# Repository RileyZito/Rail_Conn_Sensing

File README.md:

# Rail_Conn_Sensing
A circuit to sense which forks of a train track are connected for a minature train set

## Engineers
@RileyZito and @wwc559

## Subpages

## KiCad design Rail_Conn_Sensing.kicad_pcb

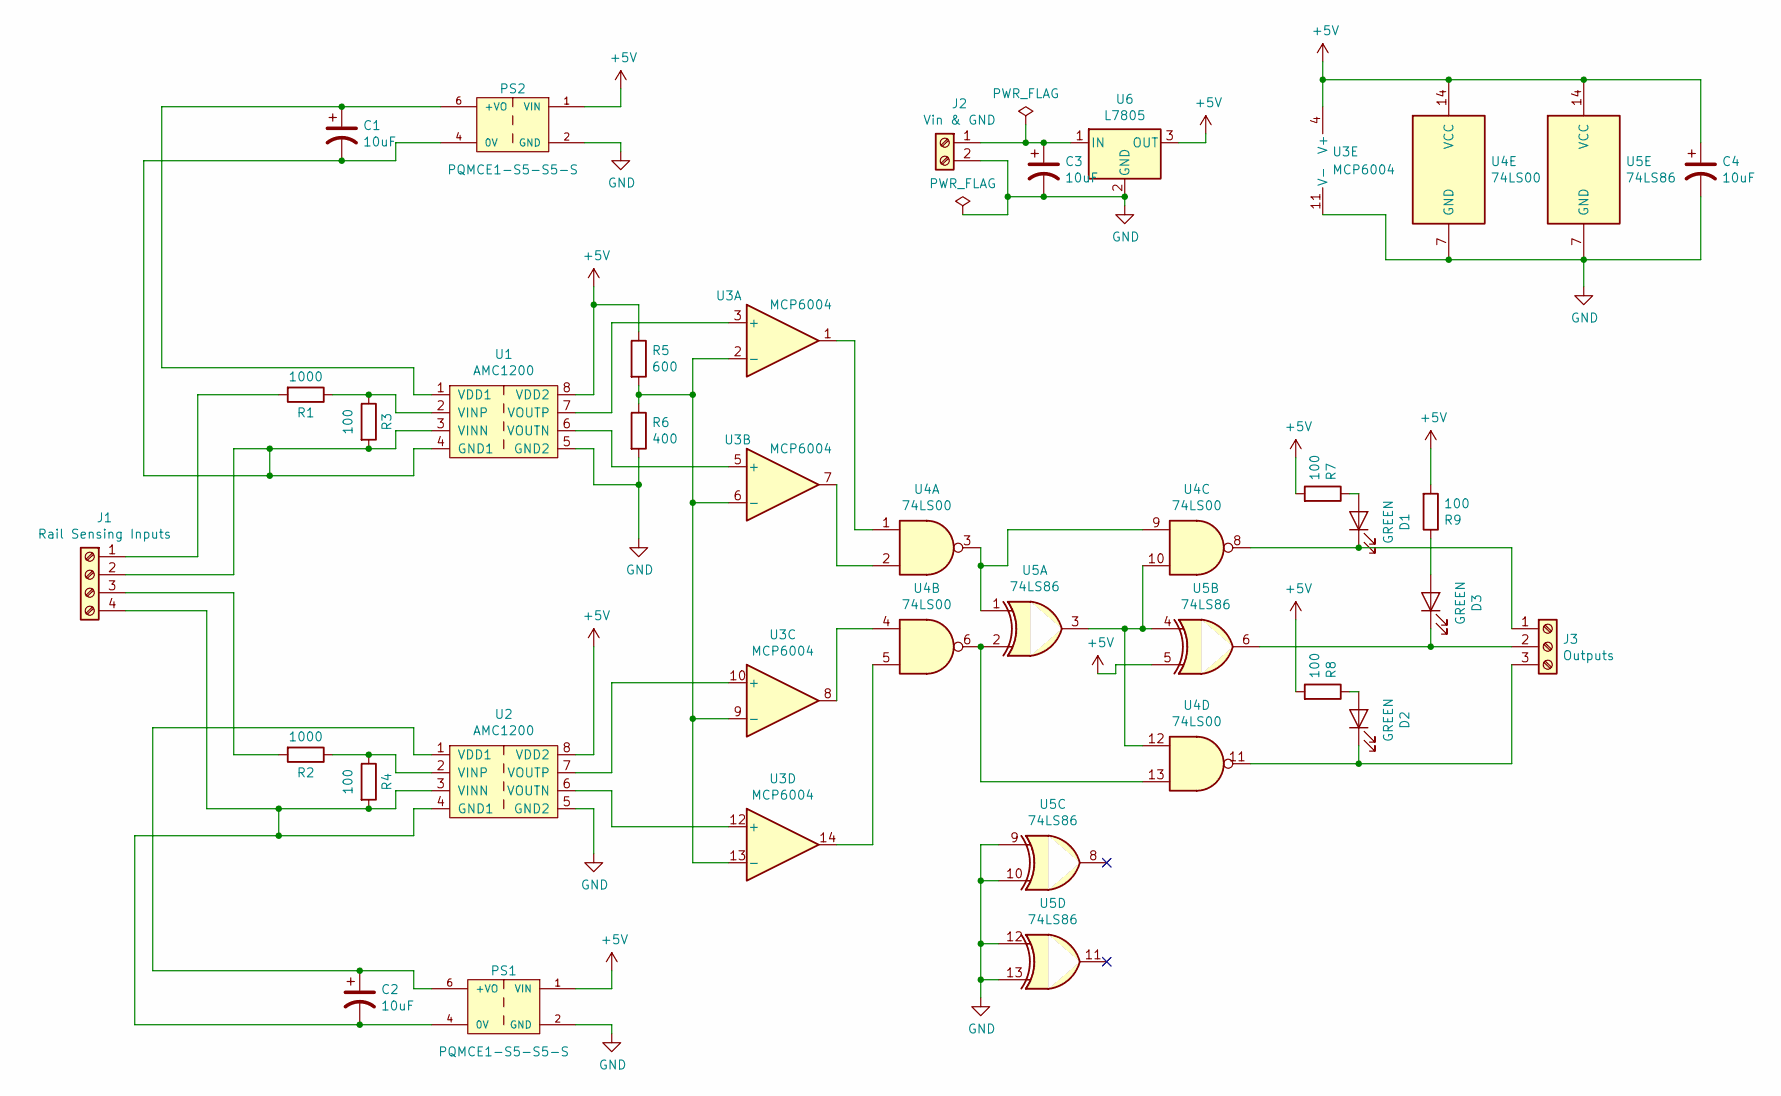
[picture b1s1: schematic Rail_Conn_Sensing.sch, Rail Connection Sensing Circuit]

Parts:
C1, C2, C3, C4: 10uF; CP_Radial_D6.3mm_P2.50mm
D1, D2, D3: GREEN; LED_D5.0mm
J1: Rail Sensing Inputs; TerminalBlock_Phoenix_PT-1,5-4-5.0-H_1x04_P5.00mm_Horizontal
J2: Vin & GND; TerminalBlock_Phoenix_PT-1,5-2-5.0-H_1x02_P5.00mm_Horizontal
J3: Outputs; TerminalBlock_Phoenix_PT-1,5-3-5.0-H_1x03_P5.00mm_Horizontal
PS1, PS2: PQMCE1-S5-S5-S; CONV_PQMCE1-S5-S5-S
R1, R2: 1000; R_Axial_DIN0309_L9.0mm_D3.2mm_P15.24mm_Horizontal
R3, R4, R7, R8, R9: 100; R_Axial_DIN0309_L9.0mm_D3.2mm_P15.24mm_Horizontal
R5: 600; R_Axial_DIN0309_L9.0mm_D3.2mm_P15.24mm_Horizontal
R6: 400; R_Axial_DIN0309_L9.0mm_D3.2mm_P15.24mm_Horizontal
U1, U2: AMC1200; SOIC-8_W7.6mm
U3: MCP6004; DIP-14_W7.62mm
U4: 74LS00; DIP-14_W7.62mm
U5: 74LS86; DIP-14_W7.62mm
U6: L7805; TO-220-3_Horizontal_TabDown

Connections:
+5V: C4.1, PS1.1 (VIN), PS2.1 (VIN), R5.1, R7.2, R8.2, R9.2, U1.8 (VDD2), U2.8 (VDD2), U3.4 (V+), U4.14 (VCC), U5.5, U5.14 (VCC), U6.3 (OUT)
GND: C3.2, C4.2, J2.2, PS1.2 (GND), PS2.2 (GND), R6.2, U1.5 (GND2), U2.5 (GND2), U3.11 (V-), U4.7 (GND), U5.7 (GND), U5.9, U5.10, U5.12, U5.13, U6.2 (GND)
unnamed: C1.1, PS2.6 (+VO), U1.1 (VDD1)
unnamed: C1.2, J1.2, PS2.4 (0V), R3.2, U1.3 (VINN), U1.4 (GND1)
unnamed: C2.1, PS1.6 (+VO), U2.1 (VDD1)
unnamed: C2.2, J1.4, PS1.4 (0V), R4.2, U2.3 (VINN), U2.4 (GND1)
unnamed: C3.1, J2.1, U6.1 (IN)
unnamed: D1.1 (K), J3.1, U4.8
unnamed: D1.2 (A), R7.1
unnamed: D2.1 (K), J3.3, U4.11
unnamed: D2.2 (A), R8.1
unnamed: D3.1 (K), J3.2, U5.6
unnamed: D3.2 (A), R9.1
unnamed: J1.1, R1.2
unnamed: J1.3, R2.2
unnamed: R1.1, R3.1, U1.2 (VINP)
unnamed: R2.1, R4.1, U2.2 (VINP)
unnamed: R5.2, R6.1, U3.2 (-), U3.6 (-), U3.9 (-), U3.13 (-)
unnamed: U1.6 (VOUTN), U3.5 (+)
unnamed: U1.7 (VOUTP), U3.3 (+)
unnamed: U2.6 (VOUTN), U3.12 (+)
unnamed: U2.7 (VOUTP), U3.10 (+)
unnamed: U3.1, U4.1
unnamed: U3.7, U4.2
unnamed: U3.8, U4.4
unnamed: U3.14, U4.5
unnamed: U4.3, U4.9, U5.1
unnamed: U4.10, U4.12, U5.3, U5.4
unnamed: U4.6, U4.13, U5.2

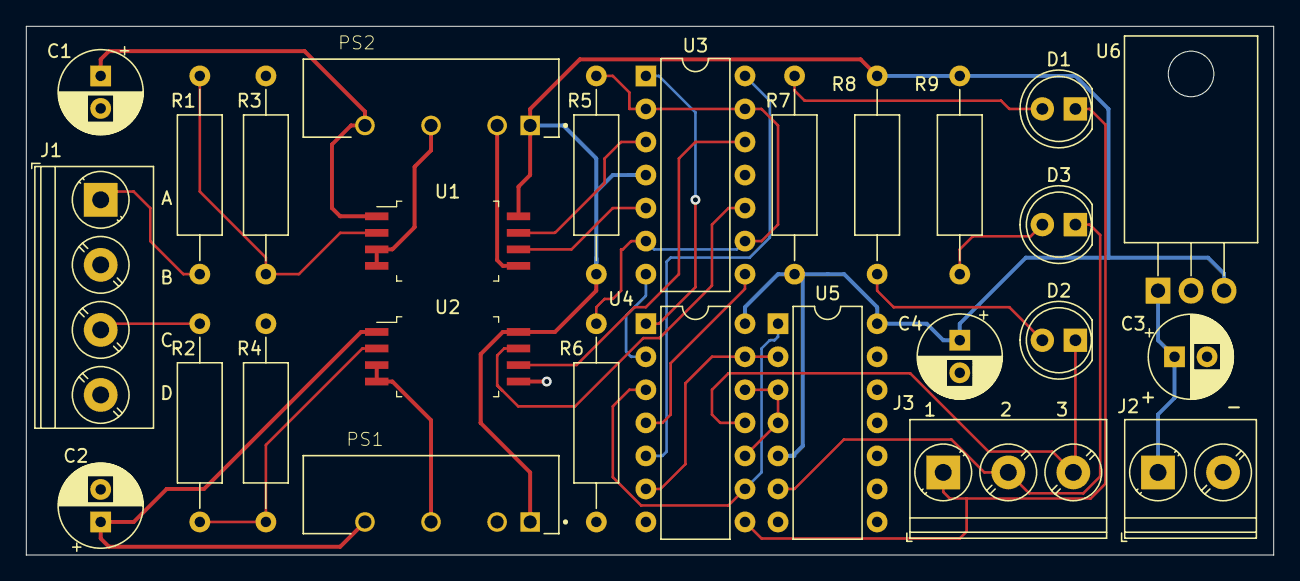
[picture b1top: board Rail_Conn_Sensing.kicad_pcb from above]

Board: 2 copper layers, 95.9 x 40.6 mm, 27 parts (0 on the bottom side), 29 nets.

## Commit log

2020-06-26 Upload version 1 of schematic
2020-06-26 Upload version 2 files with footprints
2020-06-26 Create pcb layout and part assignment
2020-06-29 Modified pcb layout
2020-06-30 Modify placement of parts on PCB
2020-06-30 Add pdf of schematic and pcb for reference
2020-07-03 Add power traces to pcb
2020-07-03 Add signal wires and ground fill for pcb
2020-07-03 Fix up wires and move silk screen labels
2020-07-06 Add connections to ground for floating unused input pins
2020-07-11 Add silkscreen for board name and input/output labels
2020-07-17 Add bill of materials
2020-07-24 Add images folder
